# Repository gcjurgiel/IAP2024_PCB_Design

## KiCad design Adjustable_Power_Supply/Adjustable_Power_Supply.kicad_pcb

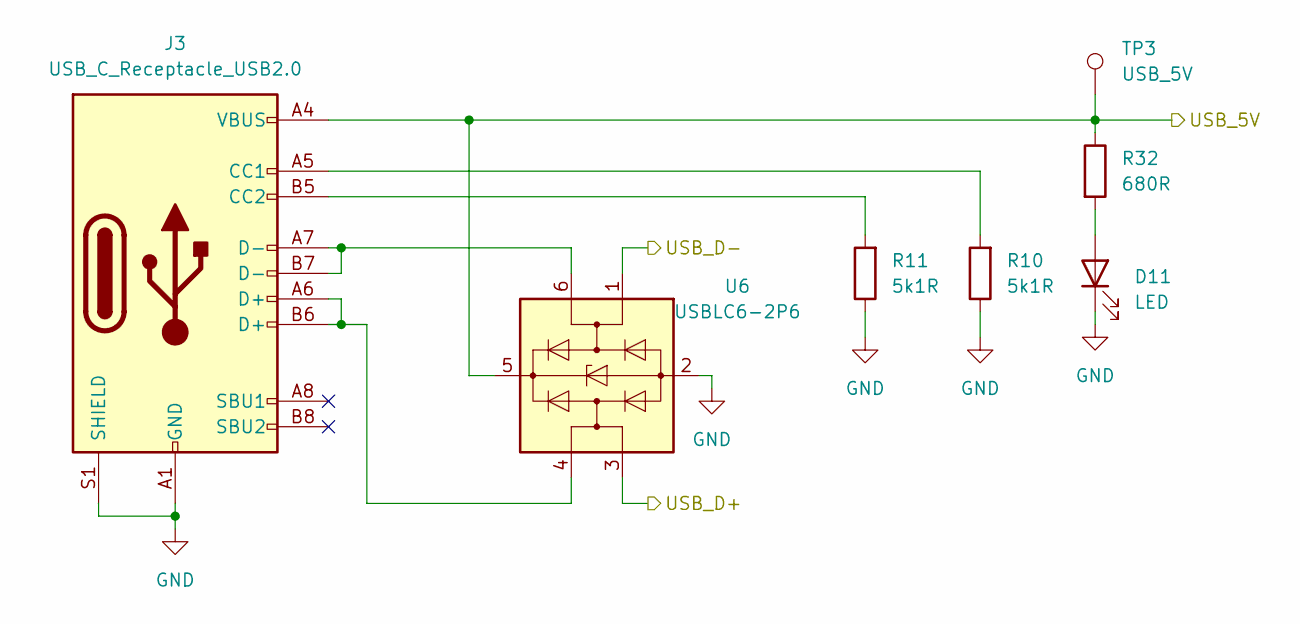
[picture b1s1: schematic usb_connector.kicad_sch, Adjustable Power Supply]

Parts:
D11: LED; LED_0603_1608Metric_Pad1.05x0.95mm_HandSolder; MPN LTST-C190GKT; Digikey PN 160-1183-1-ND
J3: USB_C_Receptacle_USB2.0; USB_C_Receptacle_GCT_USB4085; MPN 2073-USB4085-GF-ACT-ND; Digikey PN GCT
R10, R11: 5k1R; R_0603_1608Metric_Pad0.98x0.95mm_HandSolder; MPN RMCF0603FT5K10; Digikey PN RMCF0603FT5K10CT-ND
R32: 680R; R_0603_1608Metric_Pad0.98x0.95mm_HandSolder; MPN RMCF0603FT680R; Digikey PN RMCF0603FT680RCT-ND
TP3: USB_5V; TP420X150; MPN RCWCTE; Digikey PN RMCF0603ZT0R00CT-ND
U6: USBLC6-2P6; SOT-666; MPN USBLC6-2P6; Digikey PN 497-5026-1-ND

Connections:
/Logic/USB_D+: U6.3 (I/O2); also elsewhere on the board
/Logic/USB_D-: U6.1 (I/O1); also elsewhere on the board
unnamed: J3.A5 (CC1), R10.2
unnamed: J3.B5 (CC2), R11.2
unnamed: J3.A6 (D+), J3.B6 (D+), U6.4 (I/O2)
unnamed: J3.A7 (D-), J3.B7 (D-), U6.6 (I/O1)

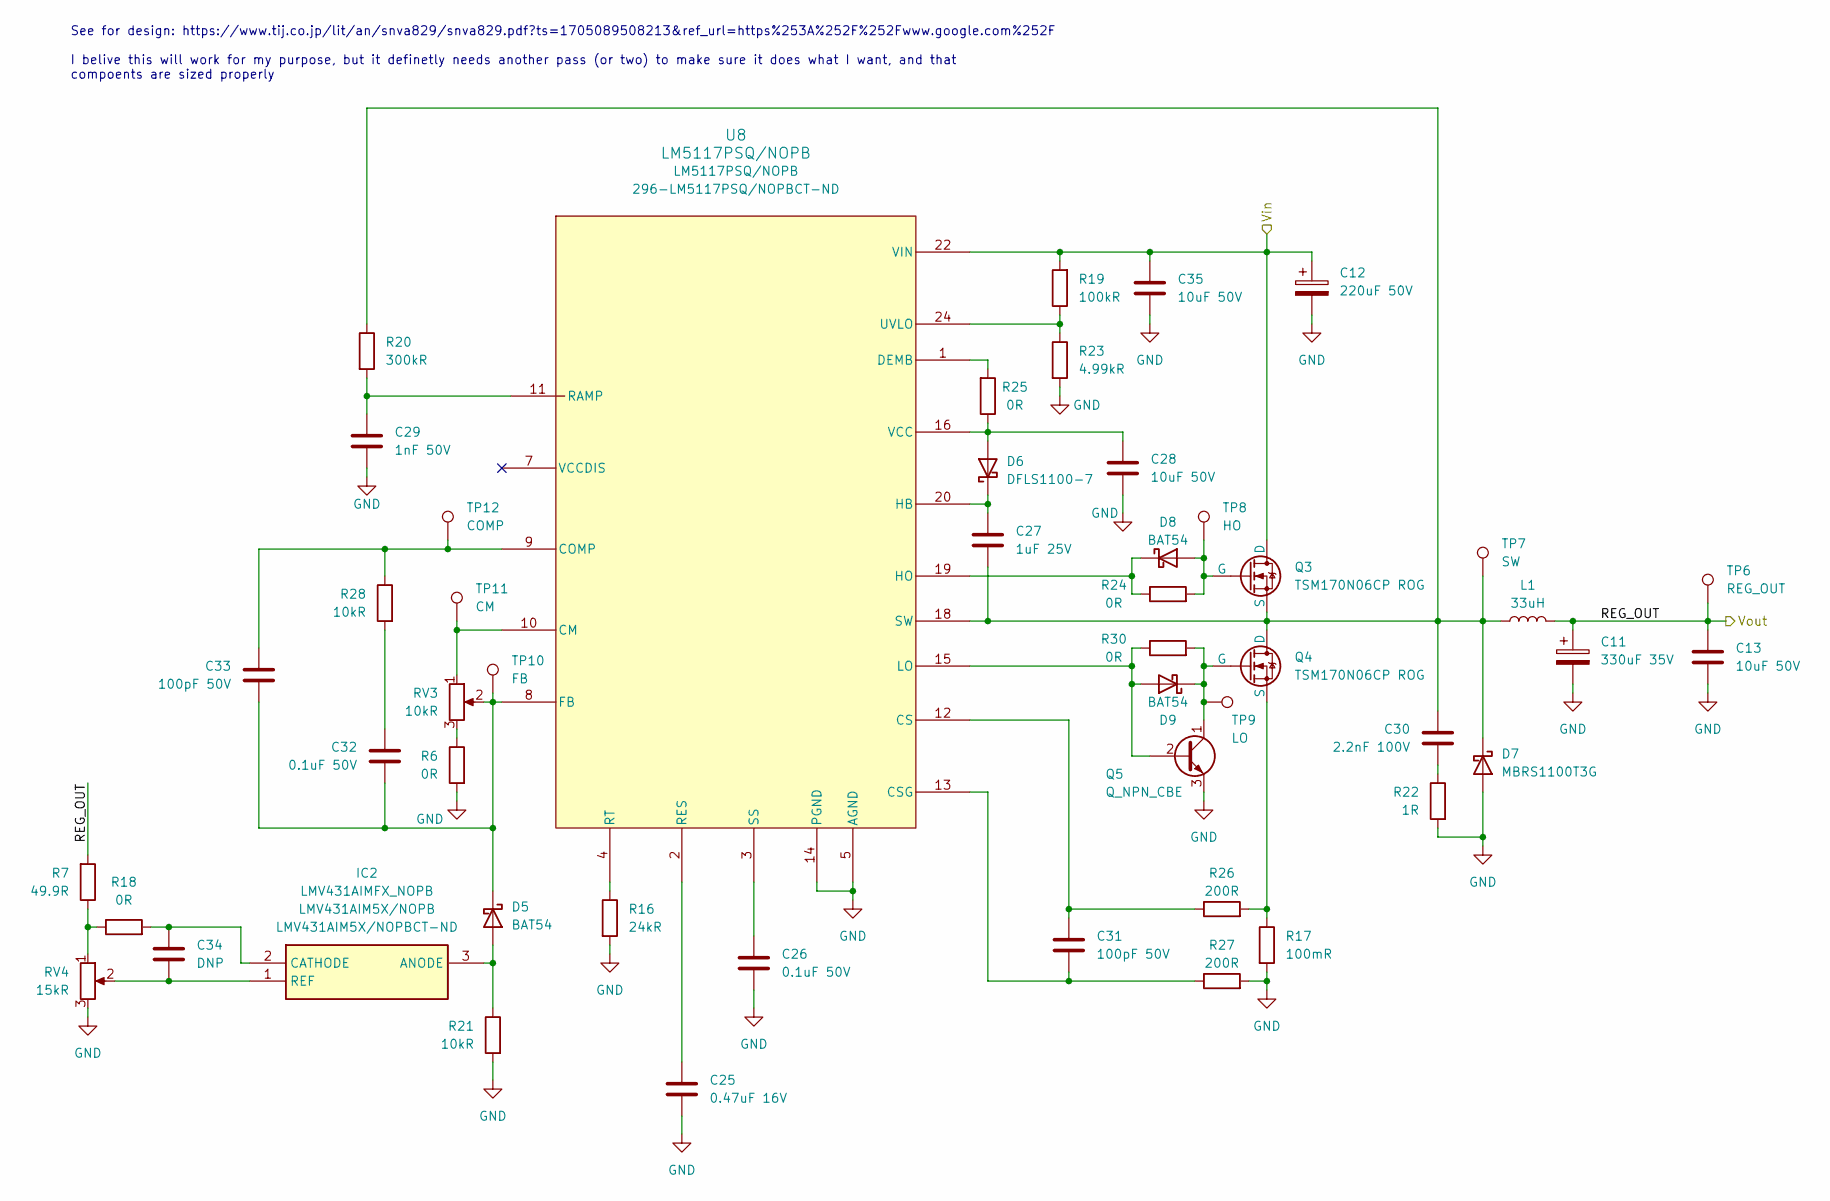
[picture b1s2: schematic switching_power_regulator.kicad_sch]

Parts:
C11: 330uF 35V; CP_Elec_10x10; MPN 35SVPK330M; Digikey PN P122136CT-ND
C12: 220uF 50V; CP_Elec_10x10; MPN EEH-ZS1H221P; Digikey PN P124104CT-ND
C13, C28, C35: 10uF 50V; C_0603_1608Metric_Pad1.08x0.95mm_HandSolder; MPN CL31A106MBHNNNE; Digikey PN 1276-6736-1-ND
C25: 0.47uF 16V; C_0603_1608Metric_Pad1.08x0.95mm_HandSolder; MPN C1608X7R1C474K080AC; Digikey PN 445-5192-1-ND
C26, C32: 0.1uF 50V; C_0603_1608Metric_Pad1.08x0.95mm_HandSolder; MPN CL10B104KB8NNNL; Digikey PN 1276-CL10B104KB8NNNLCT-ND
C27: 1uF 25V; C_0603_1608Metric_Pad1.08x0.95mm_HandSolder; MPN CL10A105KB8NNNC; Digikey PN 1276-1860-1-ND
C29: 1nF 50V; C_0603_1608Metric_Pad1.08x0.95mm_HandSolder; MPN C0603X102K5RAC3316; Digikey PN 399-C0603X102K5RAC3316CT-ND
C30: 2.2nF 100V; C_1206_3216Metric_Pad1.33x1.80mm_HandSolder; MPN C1206C222K1RECAUTO; Digikey PN 399-C1206C222K1RECAUTOCT-ND
C31, C33: 100pF 50V; C_0603_1608Metric_Pad1.08x0.95mm_HandSolder; MPN CC0603JRNPO9BN101; Digikey PN 311-1069-1-ND
C34: DNP; C_0603_1608Metric_Pad1.08x0.95mm_HandSolder
D5, D8, D9: BAT54; SOT-23; MPN BAT54; Digikey PN 1655-BAT54CT-ND
D6: DFLS1100-7; DIO_DFLS1100-7; MPN DFLS1100-7; Digikey PN DFLS1100DICT-ND
D7: MBRS1100T3G; SMB_403A-03_ONS-L; MPN MBRS1100T3G; Digikey PN MBRS1100T3GOSCT-ND
IC2: LMV431AIMFX_NOPB; SOT-23; MPN LMV431AIM5X/NOPB; Digikey PN LMV431AIM5X/NOPBCT-ND
L1: 33uH; SRP1265A-330M; MPN SRP1265A-330M; Digikey PN SRP1265A-330MCT-ND
Q3, Q4: TSM170N06CP ROG; TO-252-2; MPN TSM170N06CP ROG; Digikey PN TSM170N06CPROGCT-ND
Q5: Q_NPN_CBE; SOT-23; MPN FMMT718TA; Digikey PN FMMT718CT-ND
R6, R18, R24, R25, R30: 0R; R_0603_1608Metric_Pad0.98x0.95mm_HandSolder; MPN RMCF0603ZT0R00; Digikey PN RMCF0603ZT0R00CT-ND
R7: 49.9R; R_0603_1608Metric_Pad0.98x0.95mm_HandSolder; MPN RMCF0603FT49R9; Digikey PN RMCF0603FT49R9CT-ND
R16: 24kR; R_0603_1608Metric_Pad0.98x0.95mm_HandSolder; MPN RMCF0603FT24K0; Digikey PN RMCF0603FT24K0CT-ND
R17: 100mR; R_2512_6332Metric_Pad1.40x3.35mm_HandSolder; MPN MFHA2512R1000FE; Digikey PN 283-MFHA2512R1000FECT-ND
R19: 100kR; R_0603_1608Metric_Pad0.98x0.95mm_HandSolder; MPN RMCF0603FT100K; Digikey PN RMCF0603FT100KCT-ND
R20: 300kR; R_0603_1608Metric_Pad0.98x0.95mm_HandSolder; MPN RMCF0603FT300K; Digikey PN RMCF0603FT300KCT-ND
R21, R28: 10kR; R_0603_1608Metric_Pad0.98x0.95mm_HandSolder; MPN RMCF0603FT10K0; Digikey PN RMCF0603FT10K0CT-ND
R22: 1R; R_0603_1608Metric_Pad0.98x0.95mm_HandSolder; MPN RMCF0603FT1R00; Digikey PN RMCF0603FT1R00CT-ND
R23: 4.99kR; R_0603_1608Metric_Pad0.98x0.95mm_HandSolder; MPN RMCF0603FT4K99; Digikey PN RMCF0603FT4K99CT-ND
R26, R27: 200R; R_0603_1608Metric_Pad0.98x0.95mm_HandSolder; MPN RMCF0603FT200R; Digikey PN RMCF0603FT200RCT-ND
RV3: 10kR; Potentiometer_TT_P0915N; MPN P0915N-FC15BR10K; Digikey PN 987-1649-ND
RV4: 15kR; Potentiometer_TT_P0915N; MPN P0915N-FC15BR10K; Digikey PN 987-1649-ND
TP6: REG_OUT; TP420X150; MPN RCWCTE; Digikey PN RMCF0603ZT0R00CT-ND
TP7: SW; TP420X150; MPN RCWCTE; Digikey PN RMCF0603ZT0R00CT-ND
TP8: HO; TP420X150; MPN RCWCTE; Digikey PN RMCF0603ZT0R00CT-ND
TP9: LO; TP420X150; MPN RCWCTE; Digikey PN RMCF0603ZT0R00CT-ND
TP10: FB; TP420X150; MPN RCWCTE; Digikey PN RMCF0603ZT0R00CT-ND
TP11: CM; TP420X150; MPN RCWCTE; Digikey PN RMCF0603ZT0R00CT-ND
TP12: COMP; TP420X150; MPN RCWCTE; Digikey PN RMCF0603ZT0R00CT-ND
U8: LM5117PSQ/NOPB; LM5117PSQ_NOPB; MPN LM5117PSQ/NOPB; Digikey PN 296-LM5117PSQ/NOPBCT-ND

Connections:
/Switching Power Regulator/REG_OUT: C11.1, C13.1, L1.2, R7.2, TP6.1; also elsewhere on the board
unnamed: C30.2, R22.1
unnamed: C32.1, R28.2
unnamed: D5.2 (A), IC2.3 (ANODE), R21.1
unnamed: C32.2, C33.2, D5.1 (K), RV3.2, TP10.1, U8.8 (FB)
unnamed: C28.1, D6.2 (A), R25.1, U8.16 (VCC)
unnamed: C27.1, D6.1 (K), U8.20 (HB)
unnamed: C27.2, C30.1, D7.1 (K), L1.1, Q3.3 (S), Q4.1 (D), R20.1, TP7.1, U8.18 (SW)
unnamed: D8.2 (A), Q3.2 (G), R24.2, TP8.1
unnamed: D8.1 (K), R24.1, U8.19 (HO)
unnamed: D9.2 (A), Q5.2 (B), R30.1, U8.15 (LO)
unnamed: D9.1 (K), Q4.2 (G), Q5.1 (C), R30.2, TP9.1
unnamed: C34.1, IC2.2 (CATHODE), R18.2
unnamed: C34.2, IC2.1 (REF), RV4.2
unnamed: Q4.3 (S), R17.1, R26.2
unnamed: R6.1, RV3.3
unnamed: R7.1, R18.1, RV4.1
unnamed: RV3.1, TP11.1, U8.10 (CM)
unnamed: C33.1, R28.1, TP12.1, U8.9 (COMP)
unnamed: C31.1, R26.1, U8.12 (CS)
unnamed: C31.2, R27.1, U8.13 (CSG)
unnamed: R25.2, U8.1 (DEMB)
unnamed: C29.1, R20.2, U8.11 (RAMP)
unnamed: C25.1, U8.2 (RES)
unnamed: R16.1, U8.4 (RT)
unnamed: C26.1, U8.3 (SS)
unnamed: R19.1, R23.1, U8.24 (UVLO)

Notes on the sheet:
See for design: https://www.tij.co.jp/lit/an/snva829/snva829.pdf?ts=1705089508213&ref_url=https%253A%252F%252Fwww.google.com%252F I belive this will work for my purpose, but it definetly needs another pass (or two) to make sure it does what I want, and that compoents are sized properly

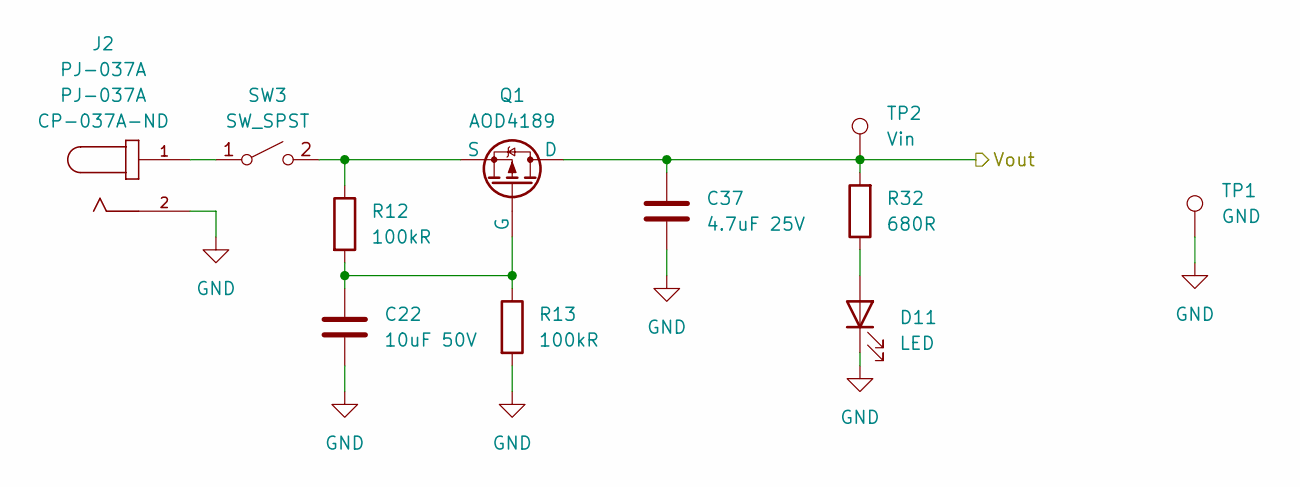
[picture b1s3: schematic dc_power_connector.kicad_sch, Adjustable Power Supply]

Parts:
C22: 10uF 50V; C_0603_1608Metric_Pad1.08x0.95mm_HandSolder; MPN CL31A106MBHNNNE; Digikey PN 1276-6736-1-ND
C37: 4.7uF 25V; C_0603_1608Metric_Pad1.08x0.95mm_HandSolder; MPN 0603W475K250XD; Digikey PN 3372-0603W475K250XDTR-ND
D11: LED; LED_0603_1608Metric_Pad1.05x0.95mm_HandSolder; MPN LTST-C190GKT; Digikey PN 160-1183-1-ND
J2: PJ-037A; MPN PJ-037A; Digikey PN CP-037A-ND
Q1: AOD4189; TO-252-2; MPN AOD4189; Digikey PN 785-1351-1-ND
R12, R13: 100kR; R_0603_1608Metric_Pad0.98x0.95mm_HandSolder; MPN RMCF0603FT100K; Digikey PN RMCF0603FT100KCT-ND
R32: 680R; R_0603_1608Metric_Pad0.98x0.95mm_HandSolder; MPN RMCF0603FT680R; Digikey PN RMCF0603FT680RCT-ND
SW3: SW_SPST; 1101M2S3CQE2; MPN 1101M2S3CQE2; Digikey PN CKN5001-ND
TP1: GND; TP420X150; MPN RCWCTE; Digikey PN RMCF0603ZT0R00CT-ND
TP2: Vin; TP420X150; MPN RCWCTE; Digikey PN RMCF0603ZT0R00CT-ND

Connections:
unnamed: C22.1, Q1.2 (G), R12.2, R13.1
unnamed: Q1.3 (S), R12.1, SW3.2 (B)
unnamed: J2.1, SW3.1 (A)

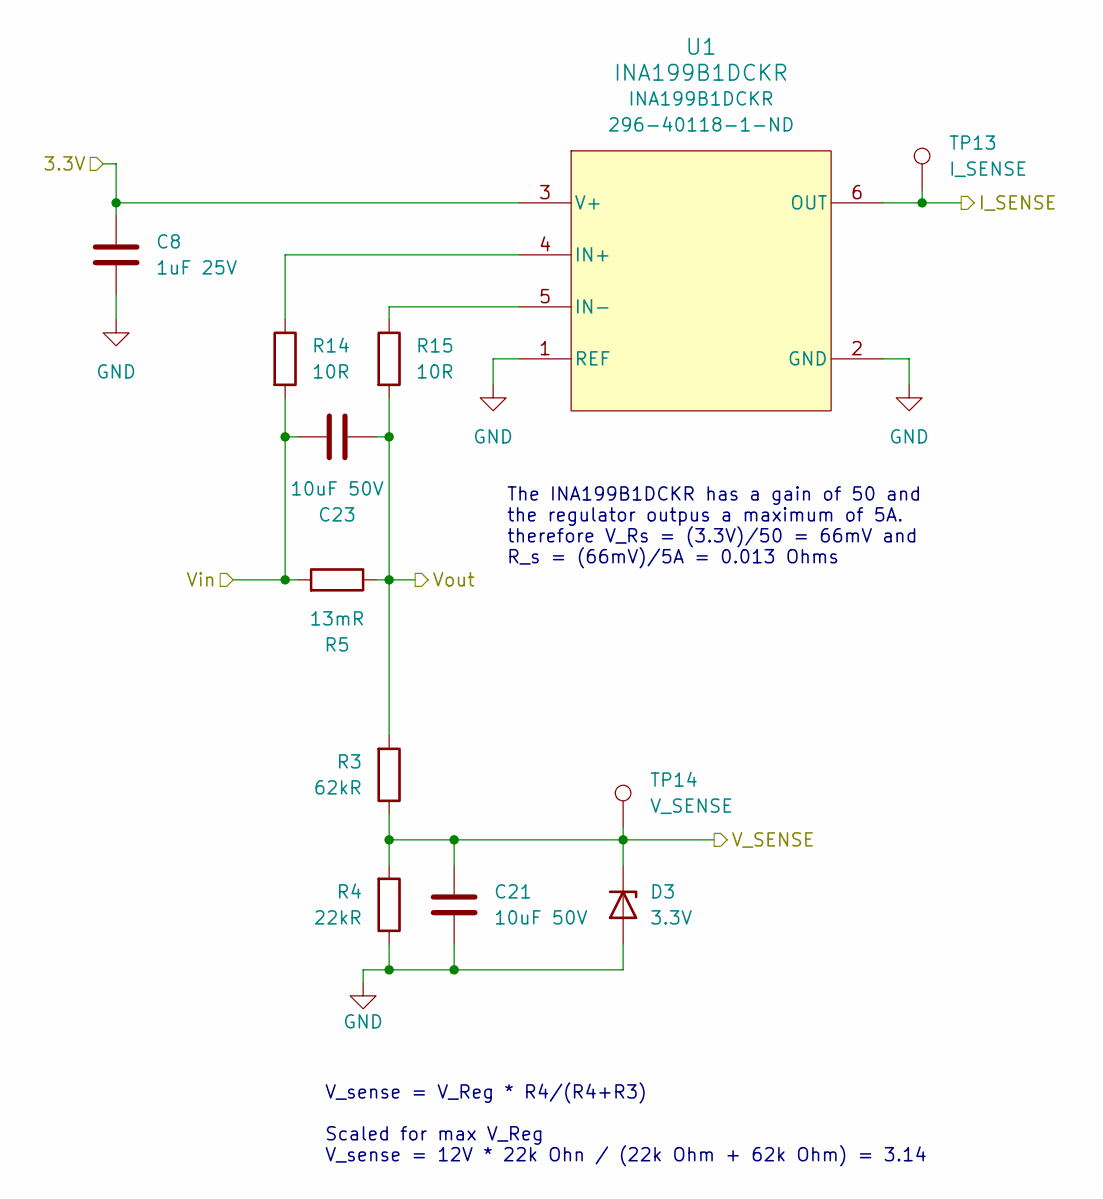
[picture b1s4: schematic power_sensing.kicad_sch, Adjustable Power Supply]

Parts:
C8: 1uF 25V; C_0603_1608Metric_Pad1.08x0.95mm_HandSolder; MPN CL10A105KB8NNNC; Digikey PN 1276-1860-1-ND
C21, C23: 10uF 50V; C_0603_1608Metric_Pad1.08x0.95mm_HandSolder; MPN CL31A106MBHNNNE; Digikey PN 1276-6736-1-ND
D3: 3.3V; SOD-123_ONS-L; MPN MMSZ4684T1G; Digikey PN MMSZ4684T1GOSCT-ND
R3: 62kR; R_0603_1608Metric_Pad0.98x0.95mm_HandSolder; MPN RMCF0603FT62K0; Digikey PN RMCF0603FT62K0CT-ND
R4: 22kR; R_0603_1608Metric_Pad0.98x0.95mm_HandSolder; MPN RMCF0603FT22K0; Digikey PN RMCF0603FT22K0CT-ND
R5: 13mR; R_2512_6332Metric_Pad1.40x3.35mm_HandSolder; MPN RLC73PV3AR013FTDG; Digikey PN 1712-RLC73PV3AR013FTDGCT-ND
R14, R15: 10R; R_0603_1608Metric_Pad0.98x0.95mm_HandSolder; MPN RMCF0603FT10R0; Digikey PN RMCF0603FT10R0CT-ND
TP13: I_SENSE; TP420X150; MPN RCWCTE; Digikey PN RMCF0603ZT0R00CT-ND
TP14: V_SENSE; TP420X150; MPN RCWCTE; Digikey PN RMCF0603ZT0R00CT-ND
U1: INA199B1DCKR; MPN INA199B1DCKR; Digikey PN 296-40118-1-ND

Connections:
/Logic/I_SENSE: TP13.1, U1.6 (OUT); also elsewhere on the board
/Logic/V_SENSE: C21.1, D3.1 (K), R3.1, R4.2, TP14.1; also elsewhere on the board
/Power Output/Vin: C23.2, R3.2, R5.1, R15.2; also elsewhere on the board
/Switching Power Regulator/REG_OUT: C23.1, R5.2, R14.2; also elsewhere on the board
unnamed: R14.1, U1.4 (IN+)
unnamed: R15.1, U1.5 (IN-)

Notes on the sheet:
The INA199B1DCKR has a gain of 50 and the regulator outpus a maximum of 5A. therefore V_Rs = (3.3V)/50 = 66mV and R_s = (66mV)/5A = 0.013 Ohms
V_sense = V_Reg * R4/(R4+R3) Scaled for max V_Reg V_sense = 12V * 22k Ohn / (22k Ohm + 62k Ohm) = 3.14

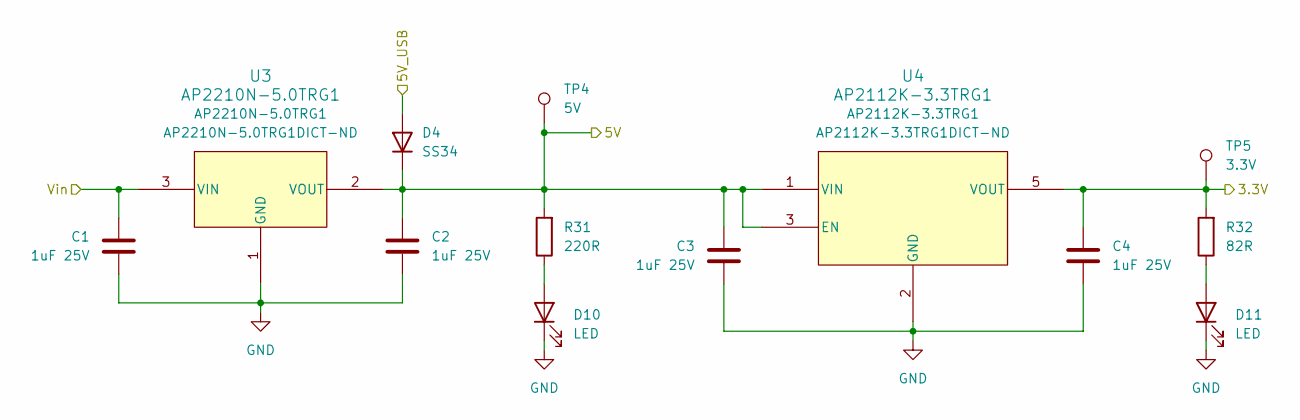
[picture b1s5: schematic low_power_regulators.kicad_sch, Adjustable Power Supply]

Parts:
C1, C2, C3, C4: 1uF 25V; C_0603_1608Metric_Pad1.08x0.95mm_HandSolder; MPN CL10A105KB8NNNC; Digikey PN 1276-1860-1-ND
D4: SS34; MPN SS34; Digikey PN SS34FSCT-ND
D10, D11: LED; LED_0603_1608Metric_Pad1.05x0.95mm_HandSolder; MPN LTST-C190GKT; Digikey PN 160-1183-1-ND
R31: 220R; R_0603_1608Metric_Pad0.98x0.95mm_HandSolder; MPN RMCF0603FT220R; Digikey PN RMCF0603FT220RCT-ND
R32: 82R; R_0603_1608Metric_Pad0.98x0.95mm_HandSolder; MPN RMCF0603FT82R0; Digikey PN RMCF0603FT82R0CT-ND
TP4: 5V; TP420X150; MPN RCWCTE; Digikey PN RMCF0603ZT0R00CT-ND
TP5: 3.3V; TP420X150; MPN RCWCTE; Digikey PN RMCF0603ZT0R00CT-ND
U3: AP2210N-5.0TRG1; MPN AP2210N-5.0TRG1; Digikey PN AP2210N-5.0TRG1DICT-ND
U4: AP2112K-3.3TRG1; MPN AP2112K-3.3TRG1; Digikey PN AP2112K-3.3TRG1DICT-ND

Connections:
unnamed 27: D4.2 (A); also elsewhere on the board
unnamed: D10.2 (A), R31.1

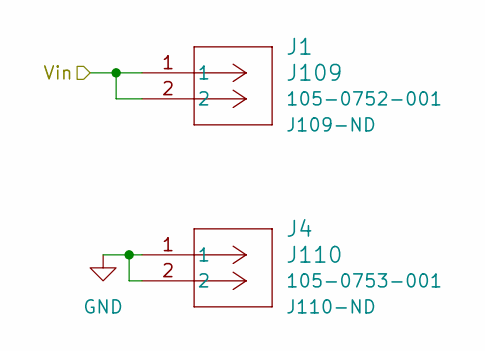
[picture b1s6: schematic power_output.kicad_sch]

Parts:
J1: J109; 105-0753-001; MPN 105-0752-001; Digikey PN J109-ND
J4: J110; 105-0753-001; MPN 105-0753-001; Digikey PN J110-ND

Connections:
/Power Output/Vin: J1.1, J1.2; also elsewhere on the board

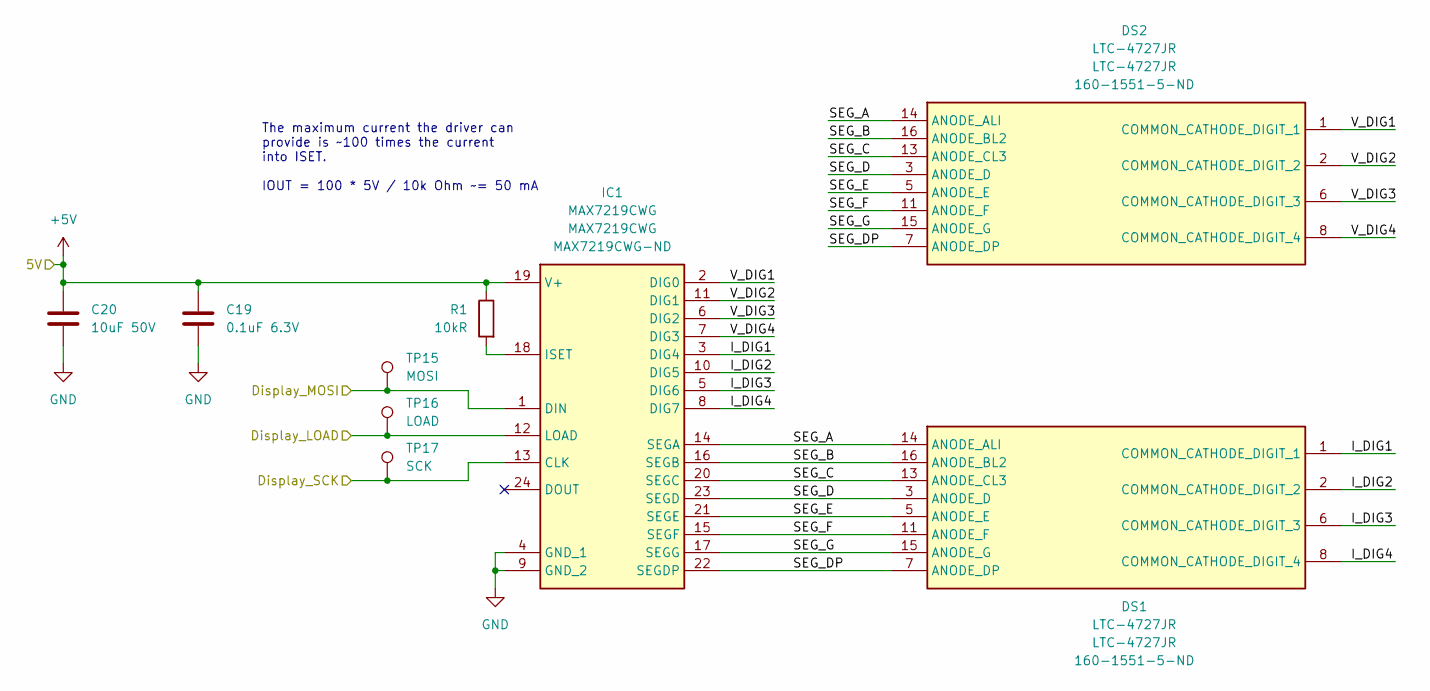
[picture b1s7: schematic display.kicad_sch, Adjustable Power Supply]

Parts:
C19: 0.1uF 6.3V; C_0603_1608Metric_Pad1.08x0.95mm_HandSolder; MPN 0603B104K500XD; Digikey PN 3372-0603B104K500XDTR-ND
C20: 10uF 50V; C_0603_1608Metric_Pad1.08x0.95mm_HandSolder; MPN CL31A106MBHNNNE; Digikey PN 1276-6736-1-ND
DS1, DS2: LTC-4727JR; MPN LTC-4727JR; Digikey PN 160-1551-5-ND
IC1: MAX7219CWG; MAX7219; MPN MAX7219CWG; Digikey PN MAX7219CWG-ND
R1: 10kR; R_0603_1608Metric_Pad0.98x0.95mm_HandSolder; MPN RMCF0603FT10K0; Digikey PN RMCF0603FT10K0CT-ND
TP15: MOSI; TP420X150; MPN RCWCTE; Digikey PN RMCF0603ZT0R00CT-ND
TP16: LOAD; TP420X150; MPN RCWCTE; Digikey PN RMCF0603ZT0R00CT-ND
TP17: SCK; TP420X150; MPN RCWCTE; Digikey PN RMCF0603ZT0R00CT-ND

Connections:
/Display/Display_LOAD: IC1.12 (LOAD), TP16.1; also elsewhere on the board
/Display/Display_MOSI: IC1.1 (DIN), TP15.1; also elsewhere on the board
/Display/Display_SCK: IC1.13 (CLK), TP17.1; also elsewhere on the board
/Display/I_DIG1: DS1.1 (COMMON_CATHODE_DIGIT_1), IC1.3 (DIG4)
/Display/I_DIG2: DS1.2 (COMMON_CATHODE_DIGIT_2), IC1.10 (DIG5)
/Display/I_DIG3: DS1.6 (COMMON_CATHODE_DIGIT_3), IC1.5 (DIG6)
/Display/I_DIG4: DS1.8 (COMMON_CATHODE_DIGIT_4), IC1.8 (DIG7)
/Display/SEG_A: DS1.14 (ANODE_ALI), DS2.14 (ANODE_ALI), IC1.14 (SEGA)
/Display/SEG_B: DS1.16 (ANODE_BL2), DS2.16 (ANODE_BL2), IC1.16 (SEGB)
/Display/SEG_C: DS1.13 (ANODE_CL3), DS2.13 (ANODE_CL3), IC1.20 (SEGC)
/Display/SEG_D: DS1.3 (ANODE_D), DS2.3 (ANODE_D), IC1.23 (SEGD)
/Display/SEG_DP: DS1.7 (ANODE_DP), DS2.7 (ANODE_DP), IC1.22 (SEGDP)
/Display/SEG_E: DS1.5 (ANODE_E), DS2.5 (ANODE_E), IC1.21 (SEGE)
/Display/SEG_F: DS1.11 (ANODE_F), DS2.11 (ANODE_F), IC1.15 (SEGF)
/Display/SEG_G: DS1.15 (ANODE_G), DS2.15 (ANODE_G), IC1.17 (SEGG)
/Display/V_DIG1: DS2.1 (COMMON_CATHODE_DIGIT_1), IC1.2 (DIG0)
/Display/V_DIG2: DS2.2 (COMMON_CATHODE_DIGIT_2), IC1.11 (DIG1)
/Display/V_DIG3: DS2.6 (COMMON_CATHODE_DIGIT_3), IC1.6 (DIG2)
/Display/V_DIG4: DS2.8 (COMMON_CATHODE_DIGIT_4), IC1.7 (DIG3)
unnamed: IC1.18 (ISET), R1.2

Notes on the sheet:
The maximum current the driver can provide is ~100 times the current into ISET. IOUT = 100 * 5V / 10k Ohm ~= 50 mA

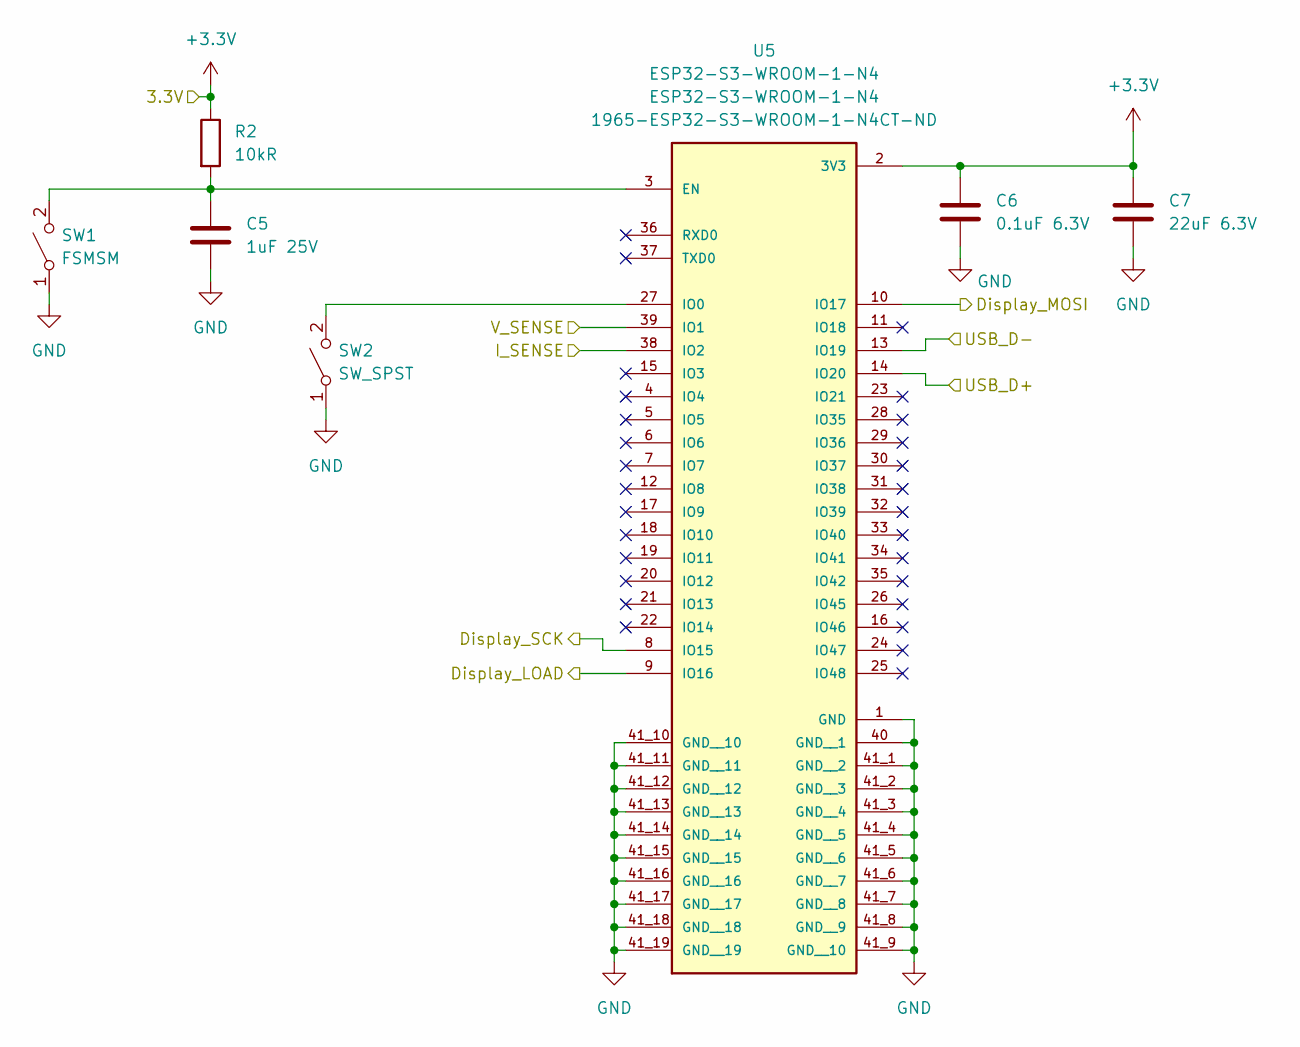
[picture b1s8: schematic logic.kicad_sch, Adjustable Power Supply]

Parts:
C5: 1uF 25V; C_0603_1608Metric_Pad1.08x0.95mm_HandSolder; MPN CL10A105KB8NNNC; Digikey PN 1276-1860-1-ND
C6: 0.1uF 6.3V; C_0603_1608Metric_Pad1.08x0.95mm_HandSolder; MPN 0603B104K500XD; Digikey PN 3372-0603B104K500XDTR-ND
C7: 22uF 6.3V; C_0603_1608Metric_Pad1.08x0.95mm_HandSolder; MPN GRM188R60J226MEA0D; Digikey PN 490-7611-1-ND
R2: 10kR; R_0603_1608Metric_Pad0.98x0.95mm_HandSolder; MPN RMCF0603FT10K0; Digikey PN RMCF0603FT10K0CT-ND
SW1: FSMSM; MPN FSMSM; Digikey PN 450-1140-ND
SW2: SW_SPST; FSMSM; MPN FSMSM; Digikey PN 450-1140-ND
U5: ESP32-S3-WROOM-1-N4; MPN ESP32-S3-WROOM-1-N4; Digikey PN 1965-ESP32-S3-WROOM-1-N4CT-ND

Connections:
/Display/Display_LOAD: U5.9 (IO16); also elsewhere on the board
/Display/Display_MOSI: U5.10 (IO17); also elsewhere on the board
/Display/Display_SCK: U5.8 (IO15); also elsewhere on the board
/Logic/I_SENSE: U5.38 (IO2); also elsewhere on the board
/Logic/USB_D+: U5.14 (IO20); also elsewhere on the board
/Logic/USB_D-: U5.13 (IO19); also elsewhere on the board
/Logic/V_SENSE: U5.39 (IO1); also elsewhere on the board
unnamed: C5.1, R2.2, SW1.2 (B), U5.3 (EN)
unnamed: SW2.2 (B), U5.27 (IO0)

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
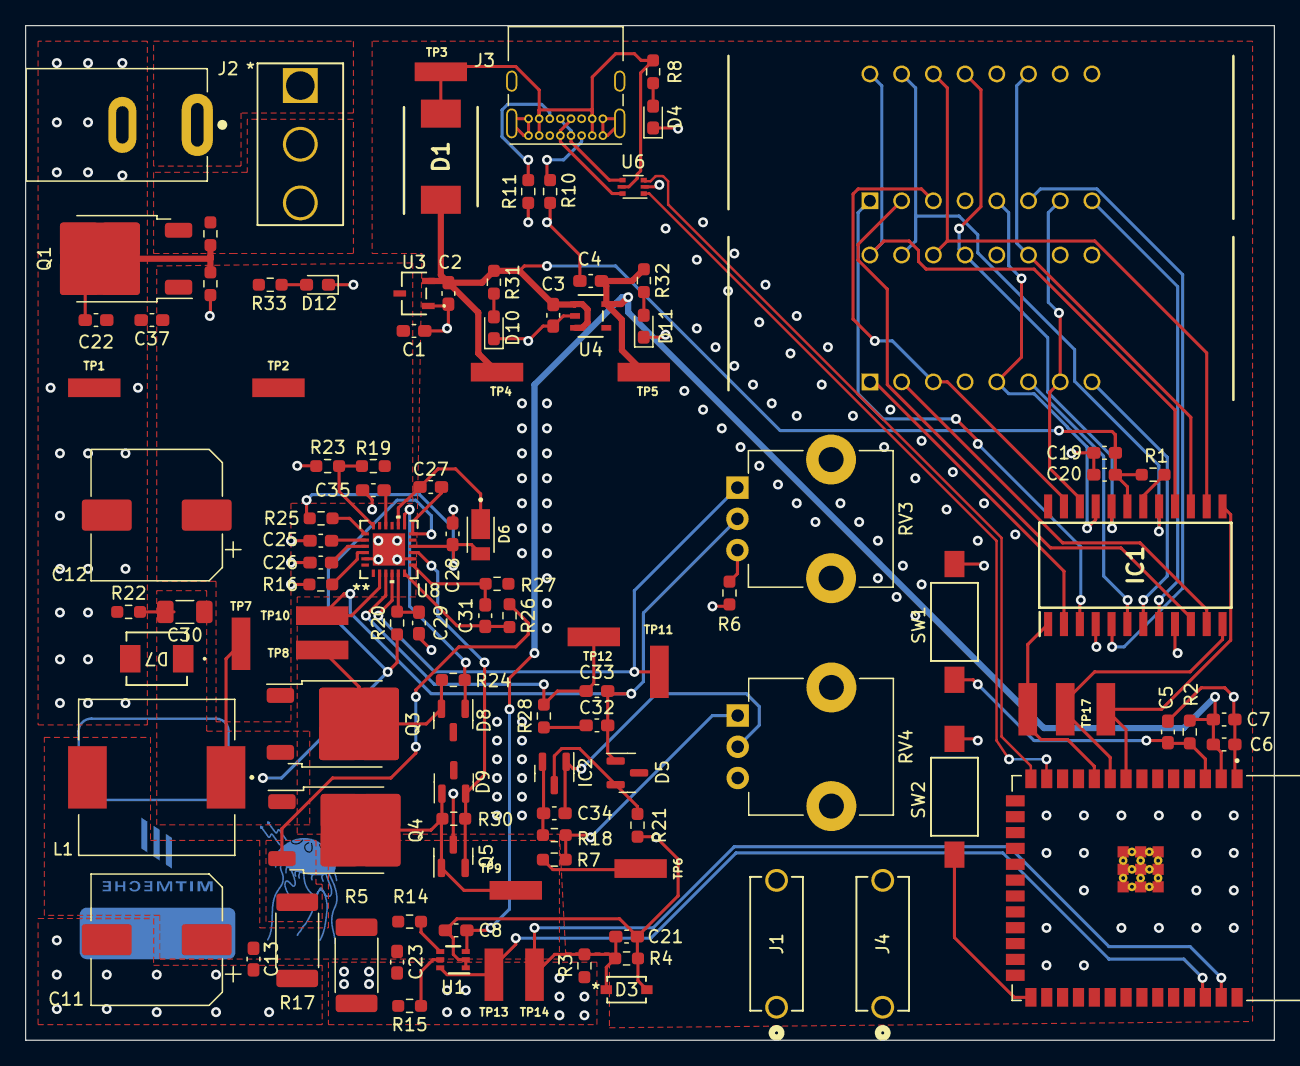
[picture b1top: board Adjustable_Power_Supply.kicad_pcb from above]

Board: 2 copper layers, 100.0 x 81.2 mm, 111 parts (0 on the bottom side), 72 nets.

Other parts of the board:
D1: SS34
D12: LED; LED_0603_1608Metric_Pad1.05x0.95mm_HandSolder
R8, R33: 680R; R_0603_1608Metric_Pad0.98x0.95mm_HandSolder

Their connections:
unnamed 27: R8.2; also elsewhere on the board
unnamed: D12.2 (A), R33.1

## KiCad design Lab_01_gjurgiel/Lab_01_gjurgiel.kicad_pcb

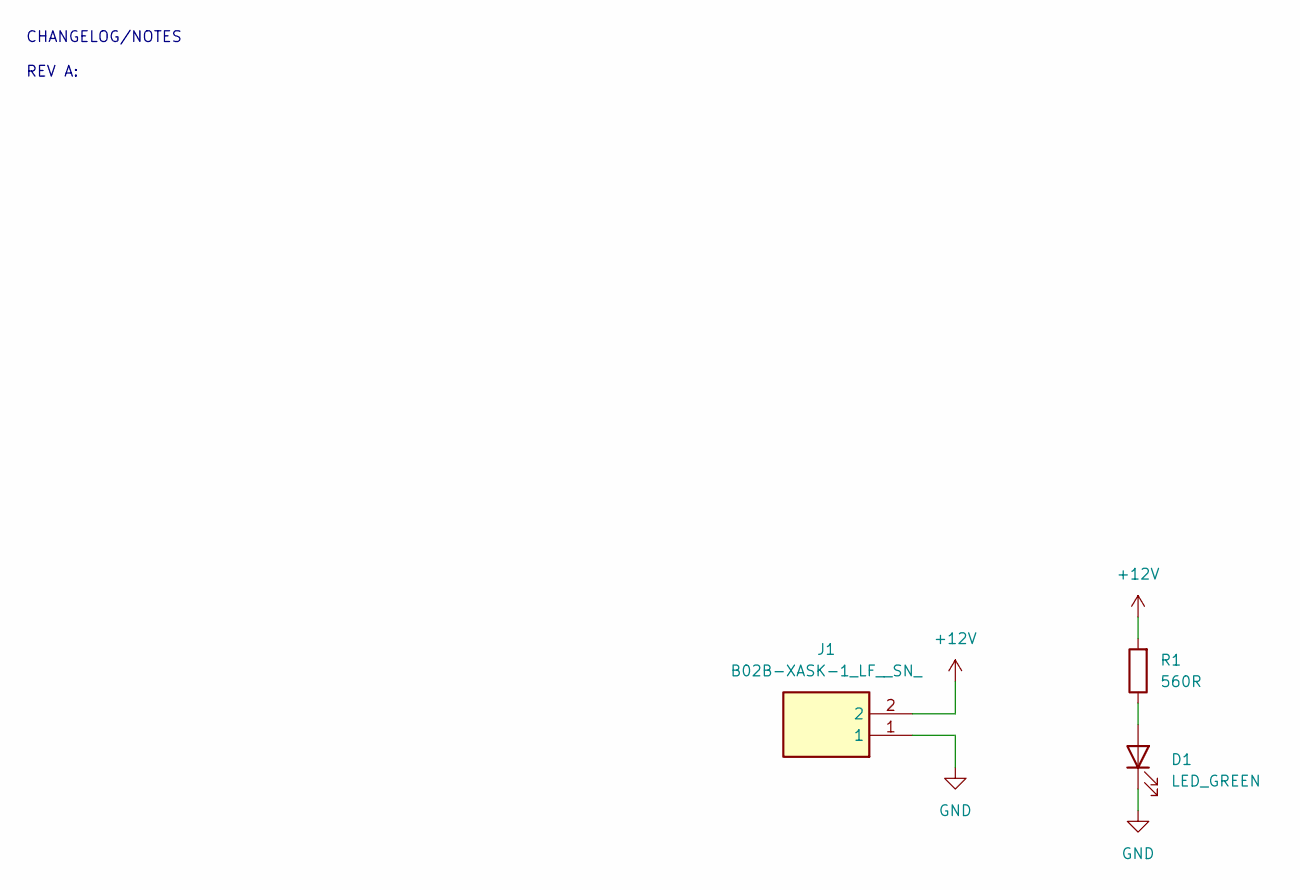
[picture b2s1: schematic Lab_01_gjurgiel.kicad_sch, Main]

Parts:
D1: LED_GREEN; LED_0603_1608Metric_Pad1.05x0.95mm_HandSolder; MPN LTST-C190GKT; Digikey PN 160-1183-1-ND
J1: B02B-XASK-1_LF__SN_; B02B-XASK-1(LF)(SN); Manufacturer_Part_Number B02B-XASK-1(LF)(SN)
R1: 560R; R_1206_3216Metric_Pad1.30x1.75mm_HandSolder; MPN RMCF1206JT560R; Digikey PN RMCF1206JT560RCT-ND

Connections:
+12V: J1.2, R1.2
GND: D1.1 (K), J1.1
unnamed: D1.2 (A), R1.1

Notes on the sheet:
CHANGELOG/NOTES REV A:

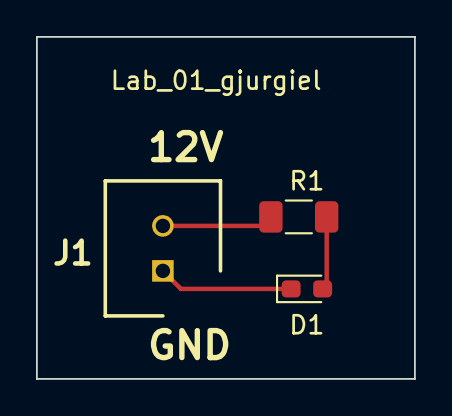
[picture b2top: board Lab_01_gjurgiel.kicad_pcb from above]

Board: 2 copper layers, 21.0 x 19.0 mm, 3 parts (0 on the bottom side), 3 nets.

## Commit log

2024-01-13 First Completed Draft
2024-01-13 Added a note
2024-01-16 Updated Footprints
2024-01-17 Room Layout
2024-01-17 Initial Switching Power Supply Routing
2024-01-17 Initial Full Board Layout
2024-01-18 Power Routing
2024-01-18 Logic Routed
2024-01-18 Stuff done in lab
2024-01-19 Fixed Cap Values
2024-01-19 First draft of routing completed
2024-01-19 Updated BOM
2024-01-19 Logos
